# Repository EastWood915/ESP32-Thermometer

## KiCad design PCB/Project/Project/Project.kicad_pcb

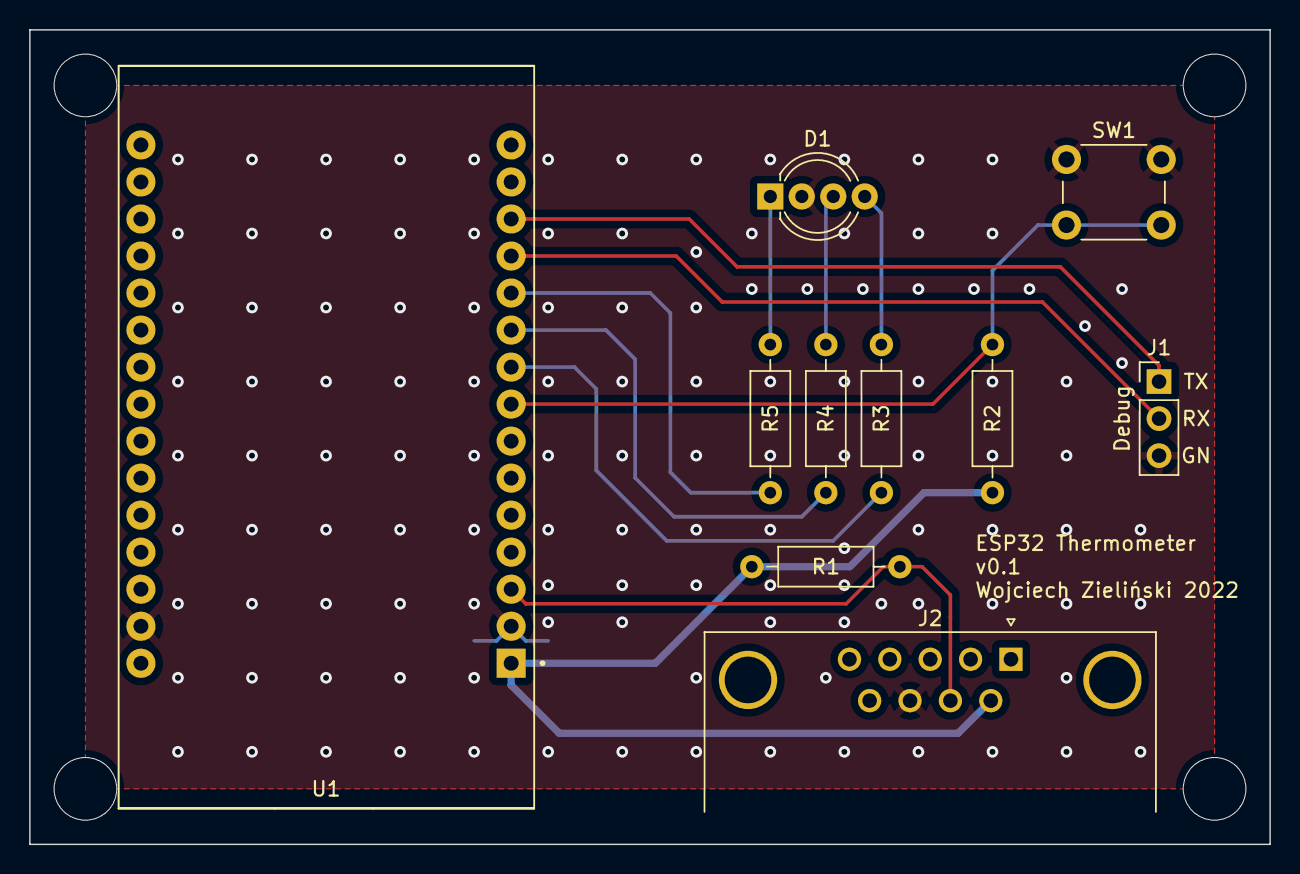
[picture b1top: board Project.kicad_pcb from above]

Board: 2 copper layers, 85.1 x 55.9 mm, 10 parts (0 on the bottom side), 12 nets.

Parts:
D1: LED_RCGB; LED_D5.0mm-4_RGB_Wide_Pins
J1: Conn_01x03_Male; PinHeader_1x03_P2.54mm_Vertical
J2: DB9_Female; DSUB-9_Female_Horizontal_P2.77x2.84mm_EdgePinOffset7.70mm_H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
R1: 4.7k; R_Axial_DIN0207_L6.3mm_D2.5mm_P10.16mm_Horizontal
R2: 3.3k; R_Axial_DIN0207_L6.3mm_D2.5mm_P10.16mm_Horizontal
R3, R4: 100; R_Axial_DIN0207_L6.3mm_D2.5mm_P10.16mm_Horizontal
R5: 330; R_Axial_DIN0207_L6.3mm_D2.5mm_P10.16mm_Horizontal
SW1: SW_Push; SW_PUSH_6mm_H5mm
U1: ESP32-DEVKIT-V1; MODULE_ESP32_DEVKIT_V1

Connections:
+3V3: J2.6, R1.1, R2.1, U1.1
BTN: R2.2, SW1.2, U1.8
DATA: J2.7, R1.2, U1.3
GND: D1.2, J1.3, J2.8, SW1.1, U1.2, U1.29
LED_BLUE: R3.2, U1.9
LED_GREEN: R4.2, U1.10
LED_RED: R5.2, U1.11
unnamed: D1.1, R5.1
unnamed: D1.3, R4.1
unnamed: D1.4, R3.1
RXD: J1.2, U1.12
TXD: J1.1, U1.13

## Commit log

2021-12-03 Started ESP-IDF project
2021-12-03 Working WiFi connection
2021-12-03 A successful dweet
2021-12-03 Added DS18B20 module to project
2021-12-03 Working temperature readout
2021-12-04 Library cleanup
2021-12-04 Parametrization and cleanup of https_get_request function
2021-12-05 Added dweet_send function
2021-12-05 Added dweet module to build system. Code cleanup.
2021-12-05 Added sample integration code
2021-12-06 Added empty led_rgb module
2021-12-06 Basic implementation. 3 colors working.
2021-12-06 Code refactoring
2021-12-06 Added yellow color
2021-12-06 Created an empty script
2021-12-06 Printing temperature in console
2021-12-06 Basic HTML. Value is displayed.
2021-12-06 Wonderful Bootstrap job
2021-12-06 Finished website
2021-12-07 Fixed timezone
2021-12-11 Added button module. Prepared header file.
2021-12-11 First implementation
2021-12-11 Button is working
2022-04-08 Added schematic and first PCB design
2022-04-08 New PCB. Added design rules.
2022-04-08 Finished routing
2022-04-08 PCB version 0.1
2022-04-08 PCB-SCH sync fix
2022-09-04 Added mounting points on PCB. Generated gerbers.
2022-10-03 Fixed Python path in settings.json
2022-10-30 Added main state machine
2022-10-31 Fixed task execution
2022-12-21 Some tweaks. Changed wifi credentials.
